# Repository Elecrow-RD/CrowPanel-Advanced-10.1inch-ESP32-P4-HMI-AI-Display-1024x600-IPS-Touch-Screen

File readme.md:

### 1, Product picture

### 2, Product version number

|      | Hardware | Software | Remark |
| ---- | -------- | -------- | ------ |
| 1    | V1.0     | V1.0     | old |
| 1    | V1.1     | V1.1     | old |
| 1    | V1.2     | V1.2     | latest |

**Version 1.1 Update**

The C6 module version 1.1 adds support for 4-wire SDIO communication. Additionally, the arrangement of the SDIO pins has been adjusted, with the pin mappings of the data lines D0–D3 changing from **IO14, IO15, IO16, IO17** to **IO17, IO16, IO15, IO14**. 

**Version 1.2 Update** 

Based on the V1.1 version, V1.2 further optimized the communication stability of the LoRa wireless module. At the same time, the signal pins of the wireless module socket were re-allocated: the original **IO53 and IO54** were adjusted to **IO27 and IO28** respectively, and correspondingly, **IO27 and IO28** were adjusted to **IO53 and IO54** respectively.

### 3, product information

| **Main Chip-ESP32-P4NRW32**                  |                                                              |
| -------------------------------------------- | ------------------------------------------------------------ |
| CPU/SoC                                      | **ESP32-P4**RISC-V 32-bit dual-core processor for HP systems, running at up to 400 MHz; RISC-V 32-bit single-core processor for LP systems, running at up to 40 MHz |
| System Memory                                | 768 KB L2MEM（HP）32 KB SRAM（LP）8 KB TCM 32 MB PSRAM       |
| Memory                                       | 128 KB ROM（HP）16 KB ROM（LP）16 MB Flash                   |
| Development Environment                      | ESP-IDF、Arduino IDE                                         |
| **Screen**                                   |                                                              |
| Size                                         | 10.1 inch                                                    |
| Resolution                                   | 1024*600                                                     |
| Display Panel                                | IPS Panel                                                    |
| Touch Panel                                  | Capacitive Touch, Single/5-point Touch                       |
| Viewing Angle                                | 178°                                                         |
| Brightness                                   | 400 cd/m²(Typ.)                                              |
| Color Depth                                  | 16.7M (8-bit)                                                |
| **Wireless Communication - Onboard Antenna** |                                                              |
| WiFi                                         | Support 2.4GHz(Wi-Fi6), 802.11a/b/g/n                        |
| Bluetooth                                    | Support Bluetooth 5.3 and BLE                                |
| Other                                        | Zigbee、LoRa、nRF2401、Matter、Thread and Wi-Fi Halow (Optional) |
| **Interface/Function**                       |                                                              |
| Interface                                    | USB2.0, UART, I2C, GPIO female headers, SD card holder, battery socket, speaker jack, camera header, module female headers, etc. |
| Function                                     | Audio amplifier, battery charge management, USB to UART, dual microphones, etc. |
| **Button/LED Indicator**                     |                                                              |
| Reset Button                                 | Yes, press to reset device                                   |
| Boot Button                                  | Yes, press and hold the power button to burn the program     |
| Power Button                                 | Switch On/Off                                                |
| PWR                                          | Device power on/off indication                               |
| CHG                                          | Lithium battery charging status, Low battery state           |
| **Other**                                    |                                                              |
| Installation method                          | All around mounting holes(M3 3.2mm), embedded, shell assembly |
| Operating temperature                        | -20~70 °C                                                    |
| Storage temperature                          | -30~80 °C                                                    |
| Power Input                                  | 5V/2A, USB or UART terminal                                  |
| Dimensions                                   | 248*147mm                                                    |

### Functional description of the product's internal interfaces:

| Pin Name | Description                                                  | Connector Type |
| :------- | :----------------------------------------------------------- | :------------- |
| SPK      | Output audio signals to connect to speakers. The main board comes with a power amplifier chip circuit. | PH2.0-2P       |
| PWR      | Power LED.                                                   |                |
| RST      | Reset button. Press it to reset the system.                  |                |
| boot     |                                                              |                |
| UART1    | Builds communication between Logic modules, including the serial communication module and the print module. | HY2.0-4P       |
| I2C      | Builds communication between Logic modules, including the serial communication module and the print module. | HY2.0-4P       |
| UART3-IN | Input power supply and serial communication functionality    | XH2.54-4P      |
| BAT      | Connect the lithium battery. (with battery charging circuit) | PH2.0-2P       |

### 4, Use the driver module

| Name | dependency library                                |
| ---- | ------------------------------------------------- |
| LVGL | lvgl/lvgl@9.1(V1.2)<br />lvgl/lvgl@8.3(V1.0/V1.1) |

### 5,Quick Start
##### ESP-IDF starts

**Note**: This is an IDF course. Before proceeding, ensure you have **Visual Studio Code** and the **IDF **environment installed. The IDF version must be **5.4.2** or higher.

1.Right-click on an empty space in the project folder and select "Open with VS Code" to open the project.

2.In the IDF plug-in, select the port, then compile and flash

### 6,Folder structure.
|--3D file： Contains 3D model files (.stp) for the hardware. These files can be used for visualization, enclosure design, or integration into CAD software.

|--Datasheet: Includes datasheets for components used in the project, providing detailed specifications, electrical characteristics, and pin configurations.

|--Eagle_SCH&PCB: Contains **Eagle CAD** schematic (`.sch`) and PCB layout (`.brd`) files. These are used for circuit design and PCB manufacturing.

|--example: Provides example code and projects to demonstrate how to use the hardware and libraries. These examples help users get started quickly.

|--factory_firmware: Stores pre-compiled factory firmware that can be directly flashed onto the device. This ensures the device runs the default functionality.

|--factory_sourcecode:  Contains the source code for the factory firmware, allowing users to modify and rebuild the firmware as needed.

|--libraries: Includes necessary libraries required for compiling and running the project. These libraries provide drivers and additional functionalities for the hardware.

### 7,Pin definition

#### ESP32-P4 10.1 inch and IPS Display Wiring Pins:
**DSI = Display Serial Interface**is a high-speed, low-power display interface standard defined by the MIPI Alliance, most commonly used in smartphones, tablets, Raspberry Pi devices, and embedded Linux systems.

DSI Pin connection

DSI_DATAN0--IO40

DSI_DATAN0--IO39

DSI_DATAN0--IO36

DSI_DATAN0--IO35

DSI_CLKN--IO37

DSI_CLKP--IO38

DSI_REXT--IO34

#### ESP32-P4 and Touch Driver Wiring：
i2c address: 0x5D/0x14.(The INT pin level during reset of the GT911 touch chip determines the device address.)

INT Low Level(0x5D);

INT High Level(0x14).

Pin connection

I2C1_SCL(IO46)

I2C1_SDA(IO45)

INT_TP(IO42)

RESET_TP(IO40)

#### ESP32-P4 and wireless module wiring pins：

Output voltage: 3.3V Output current: 1A max. Use: The power supply communicates with the wireless module.

Pin connection

#define RADIO_GPIO_CLK 8

#define RADIO_GPIO_MISO 7

#define RADIO_GPIO_MOSI 6

#ifdef CONFIG_BSP_SX1262_ENABLED

#define SX1262_GPIO_BUSY 9

#define SX1262_GPIO_IRQ 53

#define SX1262_GPIO_NRST 54

#define SX1262_GPIO_NSS 10

#ifdef CONFIG_BSP_NRF2401_ENABLED

#define NRF24_GPIO_IRQ 9

#define NRF24_GPIO_CE 53

#define NRF24_GPIO_CS 54

ESP32-P4 and Audio out：

Pin connection

#define AUDIO_GPIO_LRCLK    21   // GPIO pin number for LRCLK (Left-Right Clock)

#define AUDIO_GPIO_BCLK     22   // GPIO pin number for BCLK (Bit Clock)

#define AUDIO_GPIO_SDATA    23   // GPIO pin number for SDATA (Serial Data)

#define AUDIO_GPIO_CTRL     30   // GPIO pin number for audio amplifier control

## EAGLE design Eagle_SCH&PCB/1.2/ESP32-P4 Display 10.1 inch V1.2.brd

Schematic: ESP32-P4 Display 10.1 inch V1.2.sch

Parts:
C1, C2, C3, C10, C17, C86, C143, C160: 1uF; 0603
C4: 10uF/NC; 0603
C5, C7, C9, C36, C40, C41, C43, C45, C46, C50, C60, C61, C63, C72, C73, C108, C113, C115, C130, C132, C145: 100nF; C0402
C6, C8, C42, C44, C47, C48, C49, C56, C71, C107, C112, C114, C116: 10uF; C0402
C11, C15, C19, C20, C21, C35, C37, C52, C53, C54, C75, C76, C77, C80, C81, C82, C84, C135, C147, C150, C151, C152, C154, C156, C157, C158, C162, C170: 100nF; 0603
C12, C27, C28, C32: 10uF/10V+; 0603
C13, C18: 22uF; C0805
C14, C16, C38, C74, C78, C79, C83, C149, C153, C155, C159: 10uF; 0603
C22, C102: 1uF_NC; 0603
C23, C24, C103, C104: 47uF_NC; 0603
C25, C69, C89, C101, C163, C164, C165, C166, C167, C168, C169: 22pF; C0402
C26, C31: 22pF; 0603
C29, C30: 12pF; C0402
C33, C34: 15pF; C0402
C39: 100nF_NC; C0402
C51, C55, C57, C58, C59, C64, C65, C66, C117, C118, C119, C120, C121, C122, C123, C124, C125, C126, C127, C128, C129, C131, C133, C137, C138, C139, C140, C141, C142, C146: 1uF; C0402
C62: 10nF; C0402
C67, C68, C85, C105, C106, C161: 1nF; 0603
C70: 10UF; 0603
C87: 15pF; 0603
C88: 10UF_NC; 0603
C90, C99, C110: 10uF/25V; 0603
C91, C100, C111: 100nF/50V; 0603
C92: 22uF/16V; C0805
C93: 10nF/25V; 0603
C94: 10uF/25V; C0402
C95: 100nF/50V; C0402
C96, C97: 1uF/25V; 0603
C98, C109: 1uF/50V; 0603
C134, C148: 47uF; 0603
C136, C144: 22uF; 0805
C171, C172, C173, C174, C175, C176, C177: NC; C0402
D1: KT-0603RYG; LED_KT-0603RYG
D2, D007, D10: DSS34; D_SOD123FL
D003: NC/DSS34; D_SOD123FL
D4, D008, D11: 1N5817WS; D_SOD323
D005, D012, D013, D015, D017, D018: LMBR140ET1G
D14: Red; LED0603
D016: MM1W18_18V; LMSZ5233BT1G
D020: LMSZ5233BT1G_-6V; LMSZ5233BT1G
FB2, FB3, FB10, FB11: 1K/磁珠_NC; L0603
FB4, FB5, FB6, FB13: 0R/800mA; L0402
FB7, FB8, FB9, FB12: 1K/磁珠; L0603
FB14: 0R/800mA; R0402
FB15, FB17, FB18, FB19, FB20: 0R/2A; L0603
FB16: 0R/800mA_NC; L0603
FB21: 0R/2A; L0805
FPC1: AFC24-S24FIA-00; FPC-SMD_P0.50-24P_QCHF-SM-H2.0
FPC2: FPC-6PIN-0.5MM
IC1: ESP32-C6-MINI-1-N4; ESP32C6MINI1N4
IC2: ME6211C18M5G-N; SOT95P282X145-5N
IC3: ME6211C28M5G-N; SOT95P282X145-5N
IC4: ME6211C18M5G-N_NC; SOT95P282X145-5N
IC5: ES7210; QFN40P400X400X80-33N
IC6: ES8311; QFN40P300X300X60-21N
IC7, IC8: ME6211C33M5G-N; SOT95P282X145-5N
IC11: W25Q128JVSIQ; SOIC127P790X216-8N
J1, J16: TYPEC-3.0-16P-SMD; USB-3.0TYPEC-SMD
J2, J13: HY2.0-4P-SMT; CONNECTOR_4P-SMD-2.0
J3, J4, J6: PH2.0WT-2PIN
J5: HOLDER-MICROSD-9P; 9P-SMD-W/-RING
J7: CONN_12X22X12-SMD1; 2X12-SMD1
J8: HC-PZ200-8.7L-1X4PZ1; TEST-PIN-4-2.0MM
J9, J11: HEADER-7P-18.28X2.5; H7-2.54-18.28X2.5X5MM
J10: XH2.54-4P-SMT; XH2.54-4P-SMD
J12, J14, J15, J17: THO-M3.25MM-HOLE; THO-M3.2*5MM-HOLE
J21: C23398852_30P_0.5MM_下接_FC-05A30P11H20
K3, K4: KEY-4.5X4.5; KEY-4.5X4.5-SMD
L1, L6: 2.2μH_C5179446; 1008(2520)
L2, L5: 4.7uH_C45385206_2.4A; 1008(2520)
L3: 0R; L0603
L4: NC; L0603
P1, P2, P3, P5, P6, P7, P8, P9, P10, P11, P13, P14, P15, P18, P19, P20, P21, P25, P26, P28, P31, P32, P33, P34, P35, P36, P39, P40, P41, P43, P44, P46, P47, P51, P54, P55, P56, P63, P64, P66, P67, P68, P69, P70, P72, P73, P77: TEST_PADPAD-1.5MM; TEST_PAD-1.5MM
Q1, Q2, Q4, Q6, Q7, Q8, Q9: BSS138W_SOT323; MOS_SOT323
Q3, Q5: XR65P02D; PDFN3333
Q10, Q11: AO3401_NC; PMOS_SOT23
R1, R5, R9, R18, R53, R54, R61, R66, R67, R71, R77, R87, R91, R106, R116, R160, R180, R181: 10K; R0603@1
R2, R165: 100K; R0603@1
R3, R4, R17, R26, R47, R50, R96, R101: 5.1K; R0603@1
R6, R7, R8, R10, R13, R24, R55, R60, R65, R76, R103, R118, R119, R164, R184, R186: 0R; R0603@1
R11: 22.1K; R0603
R12, R19, R20, R36, R37, R38, R39, R41, R42, R43, R44, R70, R80, R88, R89, R90, R92, R95, R99, R100, R102, R104, R105, R109, R110, R111, R124, R125, R126, R128, R130, R146, R148, R170, R177, R190, R191, R192, R193: 0R; R0402
R14, R21: NC/499K; R0603
R15, R27, R28, R29, R30, R33, R72, R73, R140, R333: 10K; R0402
R16, R31, R32, R69: 2K; R0603-SP
R22, R45, R46, R51, R52, R56, R57, R58, R59, R62, R78: 4.7K; R0603@1
R23: 0R; C0402
R25: 0R; R0603-SP
R34, R133, R135, R136, R137, R138: 22R; R0402
R35: NC/10M; R0402
R40, R107, R127, R161, R162: 0R_NC; R0402
R48, R49, R151, R194, R216, R217, R332: 0R; 0402
R63, R64, R68, R108, R122, R123: 100K; R0402
R74, R93, R94, R97, R98: 2K; R0603@1
R75: 2K_NC; R0603@1
R79, R147, R185: OR; R0603-SP
R81, R82, R83, R84, R85, R86: 51K; R0402
R112, R113, R114, R115, R129, R149: 0R_NC; R0603@1
R117, R139: 100K_NC; R0603@1
R120, R121: 5.1K_NC; R0603@1
R131, R171: 10K/NC; R0402
R132, R134: OR/NC; R0402
R141, R142, R144, R145: OR; R0402
R143: 50K_NC; R0603-SP
R152, R153, R154, R155, R156, R157: 100R; R0402
R158: 4.02K; R0402
R159: 0.75R; R0603-SP
R163: NC; R0603-SP
R166: 210K; R0603
R167: 12K; R0603
R168: 1.5K; R0402
R169: 1K; R0402
R172, R174: 220R; R0603
R173, R175: 51K; R0603@1
R178, R179: 20K; R0603
R182: 0R; R0805
R187, R189: 39k; R0603@1
R188: 100k; R0603@1
R210: NC/10K; R0603@1
SW1: switch_6pin; SWITCH_6PIN_2P
U1: CH340K; ESOP-10-EP-150MIL
U2: TP4059-SOT23-6; SOT23-6L
U3, U13: NS4168-NC; NS4168-ESOP-8
U4: NS4263B; SOP16
U5: STC8H1K08-36I; TSSOP20
U6: MT9201; COOPER_SOT23-6
U7: ESP32-P4NRW32; IC_ESP32-P4NRW32
U8: UMH3NTN; SOP65P210X100-6N
U9: RY3420/C370754; SOT95P280X145-5N
U10: MT3406_C22462728; SOT95P280X145-5N
U16: MT3608; SOT95P280X145-6N
U176: BRAIN1_LMA3526B3811; BRAIN1_MIC-SMD_5P-L3.5-W2.7
Y2: 40MHZ; X322540MPB4SI
Y3: 24Mhz; 24MHZ_1631-24003-BTKEYA
Y4: 32.768K; NORDIC_NRF_XTAL_3215_N

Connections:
3V3$: C2.2, U1.10 (V3)
+5V_IN: D2.+, D4.+, J10.3, P14.P$1, R46.1, R51.1
+VBUS1: D10.+, D11.+, J1.A4, J1.A9, J1.B4, J1.B9, P1.P$1
+VBUS2: D007.+, D008.+, J16.A4, J16.A9, J16.B4, J16.B9, P77.P$1
ADC_AVDD_3V3: C132.1, C133.2, FB5.2, IC5.22 (VDDA), IC5.23 (VDDM)
ADC_DVDD_3V3: C130.1, C131.2, FB4.2, IC5.6 (VDDP), IC5.7 (VDDD), R73.1
ADC_VBAT: C161.2, R187.2, R188.1, U5.13 (P3.2/ADC10)
AGND: C102.2, C103.2, C104.2, C105.1, C106.1, C134.1, C143.1, C148.1, C154.2, FB19.2, FB21.2, J4.P$3, J4.P$4, R79.2, R143.1, R185.1, U4.2, U4.7, U4.15, U13.7 (GND), U13.9 (PE)
AGND1: C72.1, C117.1, C118.1, C119.1, C120.1, C121.1, C122.1, C127.2, C128.2, C129.2, C132.2, C133.1, C137.1, C138.2, C139.2, C142.2, C145.2, C146.1, IC5.21 (GNDA), IC6.10 (AGND), R144.1, R145.2, R171.2, R182.2, U176.P$1 (5)
AGND3: C22.2, C23.2, C24.2, C67.1, C68.1, FB20.2, U3.7 (GND), U3.9 (PE)
AUDIO_CTRL: Q10.3 (D), R117.2, R139.2
AUDIO_OUT_3V3: C134.2, C148.2, C154.1, FB15.2, U4.4, U4.13
AUDIO_OUT_SD: Q10.1 (G), R71.1, R147.1, U7.60 (GPIO30)
AUDIO_VDD1: C102.1, C103.1, C104.1, FB17.1, U13.6 (VDD)
AUDIO_VDD2: C22.1, C23.1, C24.1, FB18.1, U3.6 (VDD)
AUDIO_VDD_3V3: C152.2, C153.2, FB4.1, FB5.1, FB6.1, FB14.1, FB16.2, IC7.5 (VOUT)
AVDD_2V8: C82.2, C83.2, FPC1.1, FPC1.2, IC3.5 (VOUT)
C6_EN: C15.1, IC1.8 (EN), P39.P$1, R77.1, U7.63 (GPIO32)
C6_IO8: IC1.22 (IO8), R87.2
C6_IO9_BOOT: IC1.23 (IO9), P36.P$1
C6_RXD0: IC1.30 (RXD0), P21.P$1
C6_TXD0: IC1.31 (TXD0), P25.P$1
C6_VDD_3V3: C11.1, C14.2, IC1.3 (3V3), R76.1, R77.2, R81.1, R82.1, R83.1, R84.1, R85.1, R86.1, R87.1
CODEC_3V3: C145.1, C146.2, FB13.2, FB14.2, IC6.3 (PVDD), IC6.4 (DVDD)
CSID0_P: R153.1, U7.43 (CSI_DATAP0)
CSI_CLK_N: FPC1.19, R156.2
CSI_CLK_P: FPC1.18, R157.2
CSI_D0_N: FPC1.16, R152.2
CSI_D0_P: FPC1.15, R153.2
CSI_D1_N: FPC1.22, R154.2
CSI_D1_P: FPC1.21, R155.2
CSI_RESET: FPC1.8, Q4.2 (S), R57.2
CSI_SCL: FPC1.4, Q7.2 (S), R62.2
CSI_SDA: FPC1.5, Q6.2 (S), R56.2
DA1: J5.8 (DATA1), P47.P$1, R15.1
DA2: J5.1 (DATA2), P72.P$1, R30.1
DOVDD_1V8: C77.2, C78.2, C84.2, C85.2, FPC1.9, IC2.5 (VOUT), Q4.1 (G), Q6.1 (G), Q7.1 (G), R56.1, R57.1, R62.1, R67.2, Y3.4 (4_VDD)
DOWNLOAD_BOOT: R60.1, R106.2
DSI_CLK_N: J21.18, R100.1
DSI_CLK_P: J21.17, R102.1
DSI_DATA0_N: J21.24, R190.1
DSI_DATA0_P: J21.23, R92.1
DSI_DATA1_N: J21.21, R95.1
DSI_DATA1_P: J21.20, R99.1
DTR: R5.2, U1.4 (DTR#), U8.4 (E2)
EN_DCDC: R13.2, U7.79 (EN_DCDC)
ESP32_LDO1: C58.1, R105.2, U7.71 (VFB1/VO1)
ESP32_LDO2: C57.1, R40.2, U7.72 (VFB2/VO2)
ESP32_LDO3: C59.1, R80.2, U7.73 (VFB3/VO3)
ESP32_LDO4: C66.1, R109.2, U7.74 (VFB4/VO4)
FB_DCDC: C31.1, R14.2, R21.1, R103.1, U10.5 (FB)
FLASH_CK: IC11.6 (CLK), U7.32 (FLASH_CK)
FLASH_CS: IC11.1 (/CS), R333.1, U7.27 (FLASH_CS)
FLASH_D: IC11.5 (DI_(IO0)), U7.33 (FLASH_D)
FLASH_HOLD: IC11.7 (/HOLD_OR_/RESET_(IO3)), U7.31 (FLASH_HOLD)
FLASH_Q: IC11.2 (DO_(IO1)), U7.28 (FLASH_Q)
FLASH_WP: IC11.3 (/WP_(IO2)), U7.29 (FLASH_WP)
GND: C1.1, C2.1, C3.1, C4.1, C5.2, C6.1, C7.2, C8.1, C9.2, C10.1, C11.2, C12.2, C13.2, C14.1, C15.2, C16.1, C17.1, C18.2, C19.2, C20.1, C21.1, C25.2, C27.1, C28.2, C29.2, C30.2, C32.1, C33.2, C34.1, C35.1, C36.2, C37.1, C38.1, C39.2, C40.2, C41.2, C42.1, C43.2, C44.1, C45.2, C46.2, C47.1, C48.1, C49.1, C50.2, C51.2, C52.1, C53.1, C54.1, C55.2, C56.1, C57.2, C58.2, C59.2, C60.2, C61.2, C62.2, C63.2, C64.2, C65.2, C66.2, C69.2, C70.2, C71.1, C73.2, C74.1, C75.1, C76.1, C77.1, C78.1, C79.1, C80.1, C81.1, C82.1, C83.1, C84.1, C85.1, C86.1, C87.1, C88.2, C90.2, C91.2, C92.2, C94.2, C95.2, C98.2, C99.2, C100.2, C107.1, C108.2, C109.2, C110.2, C111.2, C112.1, C113.2, C114.1, C115.2, C116.1, C130.2, C131.1, C136.1, C144.1, C149.1, C150.1, C151.1, C152.1, C153.1, C155.1, C156.1, C157.1, C158.1, C159.1, C160.1, C161.1, C162.1, C163.2, C164.2, C165.2, C166.2, C167.2, C168.2, C169.2, C170.2, C171.1, C172.1, C173.1, C174.1, C175.1, C176.1, C177.1, D14.-, D016.2, D018.1, D020.1, FB19.1, FB20.1, FB21.1, FPC1.3, FPC1.6, FPC1.10, FPC1.12, FPC1.17, FPC1.20, FPC1.25, FPC1.26, FPC2.4, FPC2.7, FPC2.8, IC1.1 (GND_1), IC1.2 (GND_2), IC1.11 (GND_3), IC1.14 (GND_4), IC1.36 (GND_5), IC1.37 (GND_6), IC1.38 (GND_7), IC1.39 (GND_8), IC1.40 (GND_9), IC1.41 (GND_10), IC1.42 (GND_11), IC1.43 (GND_12), IC1.44 (GND_13), IC1.45 (GND_14), IC1.46 (GND_15), IC1.47 (GND_16), IC1.48 (GND_17), IC1.49 (GND_18), IC1.50 (GND_19), IC1.51 (GND_20), IC1.52 (GND_21), IC1.53 (GND_22), IC1.54 (GND_23), IC1.55 (GND_24), IC1.56 (GND_25), IC1.57 (GND_26), IC1.58 (GND_27), IC1.59 (GND_28), IC1.60 (GND_29), IC1.61 (GND_30), IC2.2 (VSS), IC3.2 (VSS), IC4.2 (VSS), IC5.8 (GNDD), IC5.33 (EP), IC6.5 (DGND), IC6.20 (CE), IC6.21 (EP), IC7.2 (VSS), IC8.2 (VSS), IC11.4 (GND), J1.A1, J1.A12, J1.B1, J1.B12, J1.P$1, J1.P$2, J1.P$3, J1.P$4, J2.4, J2.SS1, J2.SS2, J3.P$2, J3.P$3, J3.P$4, J5.6 (VSS), J5.G1, J5.G2, J5.G3, J5.G4, J6.P$3, J6.P$4, J7.7, J7.8, J7.10, J7.21, J7.22, J7.23, J7.24, J8.4, J9.6, J9.6-6 (6), J10.4, J10.5 (SS1), J10.6 (SS2), J12.P$1, J13.4, J13.SS1, J13.SS2, J14.P$1, J15.P$1, J16.A1, J16.A12, J16.B1, J16.B12, J16.P$1, J16.P$2, J16.P$3, J16.P$4, J17.P$1, J21.10, J21.13, J21.16, J21.19, J21.22, J21.25, J21.31, J21.32, K3.1, K4.1, P10.P$1, P15.P$1, P28.P$1, P31.P$1, P43.P$1, P66.P$1, P67.P$1, P68.P$1, P69.P$1, P70.P$1, R3.1, R4.2, R11.2, R16.1, R18.1, R21.2, R33.2, R64.1, R72.1, R96.1, R101.2, R104.1, R108.1, R123.1, R158.2, R159.1, R160.2, R163.1, R167.1, R169.1, R173.1, R175.1, R182.1, R188.2, SW1.1 (1_2B), SW1.6 (6_1B), U1.3 (GND), U1.EP, U2.2 (GND), U5.10 (GND), U6.2 (2-GND), U7.105 (GND), U9.2 (GND), U10.2 (GND), U16.2 (2_GND), Y2.2 (GND_1), Y2.4 (GND_2), Y3.2 (2_GND)
I2C1_SCL: FPC2.1, Q9.2 (S), R97.2, U7.88 (GPIO46)
I2C1_SCL_3V3: IC6.1 (CCLK), J11.2, J11.2-2 (2), J13.1, Q9.3 (D), R93.2, R119.1, R125.1
I2C1_SDA: FPC2.2, Q8.2 (S), R98.2, U7.87 (GPIO45)
I2C1_SDA_3V3: IC6.19 (CDATA), J11.3, J11.3-3 (3), J13.2, Q8.3 (D), R94.2, R118.1, R124.1
I2C2_SCL: Q7.3 (D), R59.2, R89.2
I2C2_SDA: Q6.3 (D), R22.2, R90.2
I2SOUT_LRCK1: R149.2, U13.2 (LRCLK)
I2SOUT_LRCK2: P35.P$1, R114.2, U3.2 (LRCLK)
I2SOUT_SCLK1: R129.2, U13.3 (BCLK)
I2SOUT_SCLK2: P34.P$1, R113.2, U3.3 (BCLK)
I2SOUT_SD1: R112.2, U13.4 (SDATA)
I2SOUT_SD2: P33.P$1, R115.2, U3.4 (SDATA)
I2S_LRCK: R114.1, R130.1, R149.1, U7.23 (GPIO21)
I2S_LRCK_N: IC5.10 (LRCK), IC6.8 (LRCK), R130.2
I2S_MCLK: R126.1, R127.1, U7.52 (GPIO24)
I2S_MCLK_N: IC5.5 (MCLK), IC6.2 (MCLK), R126.2
I2S_SCLK: R113.1, R128.1, R129.1, U7.24 (GPIO22)
I2S_SCLK_N: IC5.9 (SCLK), IC6.6 (SCLK/DMIC_SCL), R128.2
I2S_SDIN1_N: IC5.11 (SDOUT1/TDMOUT)
I2S_SDIN2: R161.1, R162.1, U7.55 (GPIO26)
I2S_SDIN2_N: IC5.12 (SDOUT2/TDMIN), R161.2
I2S_SDOUT: R111.1, R112.1, R115.1, U7.25 (GPIO23)
I2S_SDOUT_N: IC6.9 (DSDIN), R111.2
INLN: C147.1, R148.2
INLN1: R179.1, U4.6
INRN: C135.1, R146.2
INRN1: R178.1, U4.11
INT_TP: FPC2.3, R75.2, U7.83 (GPIO42)
IO1: R89.1, U7.14 (GPIO13)
IO8: R217.1, U7.8 (GPIO8)
IO9_W: R151.2, U7.10 (GPIO9)
IO10_W_BUSY: R194.2, U7.11 (GPIO10)
IO46_CSI_RESET: Q4.3 (D), R58.2, R88.2
LCD_AVDD_9V6: C92.1, C93.1, D005.2, D013.1, J21.9, P19.P$1, R166.2, R168.2
LCD_BK_EN: R160.1, U6.4 (4-EN), U7.61 (GPIO31)
LCD_BK_POWER: Q11.1 (G), R180.1, U7.58 (GPIO29)
LCD_BK_VDD: C13.1, C17.2, L5.1, Q11.3 (D), R184.2, U6.6 (6-VIN)
LCD_RESET: J21.27, R69.2, U7.82 (GPIO41)
LCD_VCOM_3V3: C94.1, C95.1, J21.30, P20.P$1, R168.1, R169.2
LCD_VDD: C37.2, C38.2, C52.2, C53.2, IC4.5 (VOUT), J21.28, J21.29, P46.P$1, R63.2, R65.1, R68.2, R122.2
LCD_VGH_18V: C99.1, C100.1, D016.1, J21.3, P18.P$1, R172.1, R173.2
LCD_VGL_-6V: C110.1, C111.1, D020.2, J21.4, P44.P$1, R174.1, R175.2
LED+: C18.1, C19.1, D003.-, D012.1, P63.P$1, R25.1, U6.5 (5-OV)
LED-: J21.7, J21.8, P64.P$1, R159.2, R163.2, U6.3 (3-FB)
MIC1N: C89.2
MIC1P: C101.2
MIC2N: C125.2, R141.2
MIC2P: C126.2, R142.2
MIC2_1: R132.2, R142.1, U176.1
MIC2_2: R131.1, R141.1, R145.1, R171.1, U176.2
MIC2_3: R134.1, R144.2, U176.3
MIC2_VDD_3V3: C72.2, FB6.2, U176.4
MIC3N: C124.1, R170.2
MIC3P: C123.1, R177.2
MIC_L/R: R131.2, U7.22 (GPIO20)
MIC_MCLK: R127.2, R134.2
MIC_SD2: R132.1, R162.2
unnamed: R1.1, U9.1 (EN)
unnamed: L1.1, U9.3 (SW)
unnamed: FB7.1, U4.12
unnamed: FB10.1, U13.8 (VOP)
unnamed: R6.1, U1.1 (UD+)
unnamed: R7.1, U1.2 (UD-)
unnamed: R5.1, U8.2 (B1)
unnamed: R9.1, U8.5 (B2)
unnamed: J1.B5, R3.2
unnamed: R8.2, U1.9 (RXD)
unnamed: R10.2, U1.8 (TXD)
unnamed: R16.2, U2.6 (PRO)
unnamed: C26.1, R2.2, R11.1, U9.5 (FB)
unnamed: L6.1, U10.3 (SW)
unnamed: C151.2, IC7.3 (CE), R181.1
unnamed: R13.1, R210.2, U10.1 (EN)
unnamed: C143.2, U4.10
unnamed: R185.2, U4.8
unnamed: D1.3, R31.1, R121.1
unnamed: D1.4, R32.1, R120.1
unnamed: D14.+, R26.1
unnamed: J21.1, J21.2, P56.P$1, R25.2
unnamed: C174.2, J9.1, J9.1-1 (1), R49.1
unnamed: C177.2, J11.1, J11.1-1 (1), R48.1
unnamed: FB8.1, U4.14
unnamed: Q5.4 (4_G), R78.1, SW1.2 (2_COM2), SW1.5 (5_COM1)
unnamed: J1.A5, R4.1
unnamed: R79.1, U4.16
unnamed: C28.1, R24.1, R210.1, U10.4 (VIN)
unnamed: R90.1, U7.13 (GPIO12)
unnamed: R88.1, U7.12 (GPIO11)
unnamed: R190.2, U7.40 (DSI_DATAN0)
unnamed: R92.2, U7.39 (DSI_DATAP0)
unnamed: C30.1, R35.1, U7.1 (GPIO1), Y4.2
unnamed: C29.1, R35.2, U7.104 (GPIO0), Y4.1
unnamed: R95.2, U7.36 (DSI_DATAN1)
unnamed: R99.2, U7.35 (DSI_DATAP1)
unnamed: R100.2, U7.37 (DSI_CLKN)
unnamed: C147.2, R179.2
unnamed: R102.2, U7.38 (DSI_CLKP)
unnamed: R103.2, U7.78 (FB_DCDC)
unnamed: R104.2, U7.34 (DSI_REXT)
unnamed: C21.2, IC4.3 (CE), R53.1
unnamed: C135.2, R178.2
unnamed: FB2.1, U3.8 (VOP)
unnamed: FB11.1, U13.5 (VON)
unnamed: FB3.1, U3.5 (VON)
unnamed: R117.1, U3.1 (CTRL)
unnamed: R118.2, U5.3 (MISO/P1.4)
unnamed: R119.2, U5.4 (SCLK/P1.5)
unnamed: R139.1, R143.2, U13.1 (CTRL)
unnamed: IC5.3 (CDATA), R124.2
unnamed: IC5.4 (CCLK), R125.2
unnamed: FB9.1, U4.3
unnamed: C157.2, IC8.3 (CE), R116.1
unnamed: R164.2, U5.12 (P3.1/ADC9)
unnamed: R186.2, U5.11 (P3.0/ADC8)
unnamed: FB12.1, U4.5
unnamed: C124.2, IC5.32 (MIC3N)
unnamed: C89.1, IC5.15 (MIC1N)
unnamed: C101.1, IC5.16 (MIC1P)
unnamed: C162.2, R189.2, U5.7 (NRST/PWM6/P5.4)
unnamed: R332.1, U7.7 (GPIO7)
unnamed: R216.1, U7.6 (GPIO6)
unnamed: R191.2, U7.80 (GPIO39)
unnamed: R192.2, U7.84 (GPIO43)
unnamed: R193.2, U7.86 (GPIO44)
unnamed: R158.1, U7.48 (CSI_REXT)
unnamed: R157.1, U7.44 (CSI_CLKP)
unnamed: R156.1, U7.45 (CSI_CLKN)
unnamed: R155.1, U7.47 (CSI_DATAP1)
unnamed: R154.1, U7.46 (CSI_DATAN1)
unnamed: R152.1, U7.42 (CSI_DATAN0)
unnamed: J16.B5, R96.2
unnamed: J16.A5, R101.1
unnamed: C176.2, J11.5, J11.5-5 (5), R151.1
unnamed: C175.2, J11.6, J11.6-6 (6), R194.1
unnamed: C123.2, IC5.31 (MIC3P)
unnamed: C122.2, IC5.30 (REFQ34)
unnamed: C121.2, IC5.29 (REFP34)
unnamed: C76.2, IC2.3 (CE), R61.1
unnamed: C81.2, IC3.3 (CE), R66.1
unnamed: C86.2, R67.1, Y3.1 (1_EN)
unnamed: C120.2, IC5.28 (MIC4P)
unnamed: C119.2, IC5.27 (MIC4N)
unnamed: C118.2, IC5.26 (MICBIAS34)
unnamed: C117.2, IC5.25 (REFQM)
unnamed: C129.1, IC5.24 (MICBIAS12)
unnamed: C125.1, IC5.20 (MIC2N)
unnamed: C126.1, IC5.19 (MIC2P)
unnamed: C127.1, IC5.18 (REFQ12)
unnamed: C128.1, IC5.17 (REFP12)
unnamed: R147.2, U4.1
unnamed: C97.2, D017.1, D018.2
unnamed: IC5.1 (AD0), R73.2
unnamed: IC5.2 (AD1), R72.2
unnamed: C139.1, IC6.14 (DACVREF)
unnamed: C137.2, IC6.16 (VMID)
unnamed: C138.1, IC6.15 (ADCVREF)
unnamed: C140.1, IC6.13 (OUTN)
unnamed: C141.1, IC6.12 (OUTP)
unnamed: C142.1, FB13.1, IC6.11 (AVDD)
unnamed: D003.+, D012.2, L5.2, U6.1 (1-SW)
unnamed: C96.1, C97.1, D013.2, L2.2, U16.1 (1_SW)
unnamed: R165.2, U16.4 (4_EN)
unnamed: C96.2, D005.1, D015.2
unnamed: C93.2, R166.1, R167.2, U16.3 (3_FB)
unnamed: C98.1, D015.1, R172.2
unnamed: C140.2, R146.1, R170.1
unnamed: C109.1, D017.2, R174.2
unnamed: C141.2, R148.1, R177.1
P4_IO2: J7.9, U7.2 (GPIO2)
P4_IO3: J7.11, U7.3 (GPIO3)
P4_IO4: J7.13, U7.4 (GPIO4)
P4_IO5: J7.15, U7.5 (GPIO5)
P4_IO25: J7.17, U7.53 (GPIO25)
P4_IO35: R55.2, U7.66 (GPIO35)
P4_IO36: R60.2, U7.68 (GPIO36)
P4_IO49: J7.19, U7.92 (GPIO49)
P4_IO50: J7.20, U7.93 (GPIO50)
P4_IO51: J7.18, U7.94 (GPIO51)
P4_IO52: J7.16, U7.95 (GPIO52)
P4_IO53: J7.14, U7.97 (GPIO53)
P4_IO54: J7.12, U7.98 (GPIO54)
P4_RST_EN: C35.2, K4.2, R54.2, U7.103 (CHIP_PU), U8.6 (C1)
P4_RXD2: R48.2, U7.57 (GPIO28)
P4_TXD2: R49.2, U7.56 (GPIO27)
P4_VBAT: C9.1, C42.2, R20.1, U7.102 (VBAT)
POWER_CHRG: R50.1, R120.2, U2.1 (CHG), U5.14 (P3.3/ADC11)
POWER_DONE: R47.1, R121.2, U2.5 (STD), U5.15 (P3.4/ADC11)
POWER_G_LED: R31.2, U5.17 (P3.6/ADC14)
POWER_R_LED: R32.2, U5.16 (P3.5/ADC13)
RESET_TP: FPC2.6, R74.2, U7.81 (GPIO40)
RTS: R9.2, U1.6 (RTS#), U8.1 (E1)
RXD0: R10.1, U7.70 (GPIO38)
RXD1: J2.1, U7.90 (GPIO48)
RXD3: Q2.2 (S), R45.2, U7.64 (GPIO33)
SD1_CMD: C168.1, J5.3 (DI), P8.P$1, R28.1, R193.1
SD1_D0: C167.1, J5.7 (DO), P6.P$1, R27.1, R191.1
SD1_SCK: C169.1, J5.5 (SCLK), P7.P$1, R140.1, R192.1
SD2_CLK: R133.2, U7.19 (GPIO18)
SD2_CLK_C6: C165.1, IC1.25 (IO19), R82.2, R133.1
SD2_CMD: R34.2, U7.20 (GPIO19)
SD2_CMD_C6: C166.1, IC1.24 (IO18), R34.1, R81.2
SD2_D0: R135.2, U7.18 (GPIO17)
SD2_D0_C6: C164.1, IC1.26 (IO20), R83.2, R135.1
SD2_D1: R136.2, U7.17 (GPIO16)
SD2_D1_C6: C163.1, IC1.27 (IO21), R84.2, R136.1
SD2_D2: R137.2, U7.16 (GPIO15)
SD2_D2_C6: C69.1, IC1.28 (IO22), R85.2, R137.1
SD2_D3: R138.2, U7.15 (GPIO14)
SD2_D3_C6: C25.1, IC1.29 (IO23), R86.2, R138.1
SDCS: J5.2 (CS), P73.P$1, R29.1, R33.1
SHLR: J21.6, P40.P$1, R122.1, R123.2
SPI2_MISO: C172.2, J9.3, J9.3-3 (3), R332.2
SPI2_MOSI: C171.2, J9.4, J9.4-4 (4), R216.2
SPI2_SCK: C173.2, J9.2, J9.2-2 (2), R217.2
SPI_BOOT: C54.2, K3.2, R55.1, R91.2, U8.3 (C2)
STBYB: J21.26, P51.P$1, R63.1, R64.2
STC8_RXD: J8.2, R186.1
STC8_TXD: J8.1, R164.1
STC8_VDD_3V3: C158.2, C159.2, C160.2, IC8.5 (VOUT), J8.3, R189.1, U5.8 (VCC), U5.9 (VREF)
TXD0: R8.1, U7.69 (GPIO37)
TXD1: J2.2, U7.89 (GPIO47)
TXD3: Q1.2 (S), R52.2, U7.65 (GPIO34)
UART_IN_RXD3: J10.2, Q2.3 (D), R46.2
UART_IN_TXD3: J10.1, Q1.3 (D), R51.2
UPDN: J21.5, P41.P$1, R68.1, R108.2
USB1_D+: J1.A6, J1.B6, P2.P$1, R6.2
USB1_D-: J1.A7, J1.B7, P3.P$1, R7.2
USB2_D+: J16.A6, J16.B6, U7.50 (DP)
USB2_D-: J16.A7, J16.B7, U7.49 (DM)
VBAT: C4.2, J3.P$1, P9.P$1, Q3.5 (5_D), Q3.6 (6_D), Q3.7 (7_D), Q3.8 (8_D), Q3.9 (9_D), R17.1, R187.1, U2.3 (BAT)
VCC5V: C155.2, C156.2, D1.1, D1.2, D2.-, D007.-, D10.-, IC8.1 (VIN), P11.P$1, Q3.1 (1_S), Q3.2 (2_S), Q3.3 (3_S), Q5.1 (1_S), Q5.2 (2_S), Q5.3 (3_S), R78.2, R116.2
VCC5V_IN: C3.2, D4.-, D008.-, D11.-, Q3.4 (4_G), R17.2, R18.2, R47.2, R50.2, U2.4 (VCC)
VCCA: C43.1, C47.2, R23.1, U7.51 (VCCA)
VDD5V: C12.1, C74.2, C75.2, C79.2, C80.2, C90.1, C91.1, C149.2, C150.2, FB15.1, FB17.2, FB18.2, IC2.1 (VIN), IC3.1 (VIN), IC7.1 (VIN), J7.2, J7.4, J7.6, L2.1, L4.2, P5.P$1, Q5.5 (5_D), Q5.6 (6_D), Q5.7 (7_D), Q5.8 (8_D), Q5.9 (9_D), Q11.2 (S), R1.2, R24.2, R26.2, R61.2, R66.2, R165.1, R180.2, R181.2, R184.1, U9.4 (VIN), U16.5 (5_IN)
VDD5V_W: C88.1, J9.7, J9.7-7 (7), L4.1
VDDA: C7.1, C8.2, R19.1, U7.101 (VDDA)
VDDPST: C36.1, C55.1, R40.1, R110.1, U7.59 (VDDPST), U7.67 (VDDPST)
VDDPST_1: C73.1, C107.2, R36.1, U7.9 (VDDPST_1)
VDDPST_2: C41.1, C44.2, R37.1, U7.21 (VDDPST_2)
VDDPST_3: C45.1, C49.2, R38.1, U7.30 (VDDPST_3)
VDDPST_4: C50.1, C56.2, R39.1, U7.62 (VDDPST_4)
VDDPST_5: C60.1, C65.1, Q8.1 (G), Q9.1 (G), R69.1, R74.1, R75.1, R97.1, R98.1, R109.1, U7.85 (VDDPST_5)
VDDPST_6: C61.1, C71.2, R41.1, U7.96 (VDDPST_6)
VDDPST_DCDC: C5.1, C6.2, R12.1, U7.77 (VDDPST_DCDC)
VDDPST_LDO: C46.1, C48.2, R70.1, U7.75 (VDDPST_LDO)
VDD_1V2: C31.2, C32.2, C144.2, L6.2, R14.1, R42.2, R43.2, R44.2
VDD_3V3: C1.2, C10.2, C16.2, C20.2, C26.2, C27.2, C136.2, FB16.1, FPC2.5, IC4.1 (VIN), J2.3, J5.4 (VDD), J7.1, J7.3, J7.5, J13.3, L1.2, L3.2, P13.P$1, Q1.1 (G), Q2.1 (G), Q10.2 (S), R2.1, R12.2, R15.2, R19.2, R20.2, R22.1, R23.2, R27.2, R28.2, R29.2, R30.2, R36.2, R37.2, R38.2, R39.2, R41.2, R45.1, R52.1, R53.2, R54.1, R58.1, R59.1, R65.2, R70.2, R71.2, R76.2, R91.1, R93.1, R94.1, R106.1, R107.2, R110.2, R140.2, U1.7 (VCC)
VDD_3V3_A: C70.1, C170.1, J9.5, J9.5-5 (5), L3.1
VDD_FLASH: C39.1, C40.1, C51.1, IC11.8 (VCC), R105.1, R107.1, R333.2
VDD_HP_0: C108.1, C112.2, R42.1, U7.26 (VDD_HP_0)
VDD_HP_2: C113.1, C114.2, R43.1, U7.76 (VDD_HP_2)
VDD_HP_3: C115.1, C116.2, R44.1, U7.91 (VDD_HP_3)
VDD_MIPI_DPHY: C62.1, C63.1, C64.1, R80.1, U7.41 (VDD_MIPI_DPHY)
VOLN: C106.2, FB11.2, FB12.2, J4.P$2, P55.P$1
VOLP: C105.2, FB9.2, FB10.2, J4.P$1, P54.P$1
VORN: C68.2, FB3.2, FB7.2, J6.P$2, P32.P$1
VORP: C67.2, FB2.2, FB8.2, J6.P$1, P26.P$1
XTAL_N: C34.2, U7.99 (XTAL_N), Y2.3 (CRYSTAL_2)
XTAL_P: C33.1, U7.100 (XTAL_P), Y2.1 (CRYSTAL_1)
XVCLK: C87.2, FPC1.11, Y3.3 (3_OUT)

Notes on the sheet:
BOOT
RESET
HIG: SPI Boot
LOW: Download Boot
HIG: ESP32-P4 Enable
LOW: ESP32-P4 Off
Power_LED
USB interface
USB TO UART
Battery and control
ESP32-C6
7.0 inch IPS interface
SD card
Wireless module
UART & I2C & GPIO extensions
PDM MIC
UART_5V_IN
I2C_OUT
UART0_OUT
ESP32-P4
ESP32-P4_POWER
CSI_Interface
I led=200mV/0.75=160mA
DSI_LED Driver
Audio_OUT
DC-DC:5V to 3V3
DC-DC:5V to 1V2
Power SW
LCD_POWER
Charge indicator control
Audio_ADC/DAC
LDO:5V to 3V3(AUDIO POWER)
ESP32 P4-Advance HMI Display 10.1 V1.0

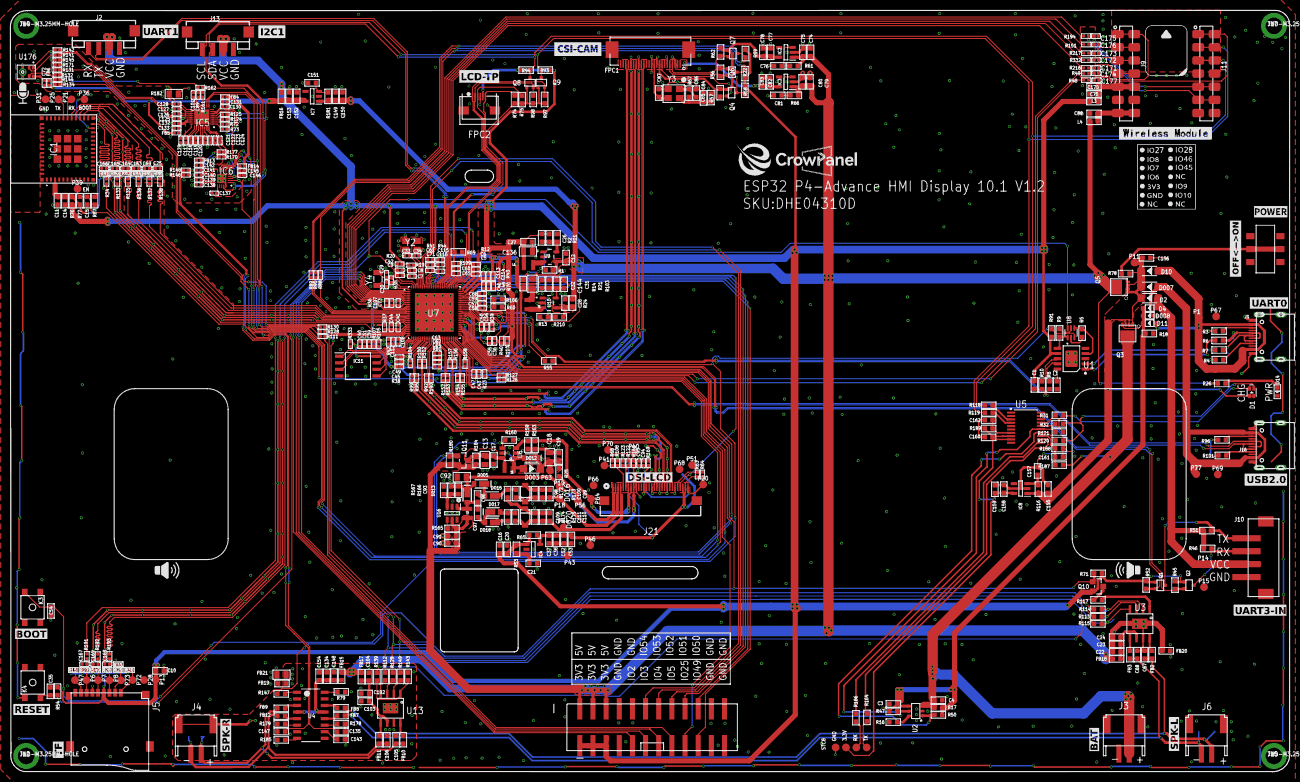
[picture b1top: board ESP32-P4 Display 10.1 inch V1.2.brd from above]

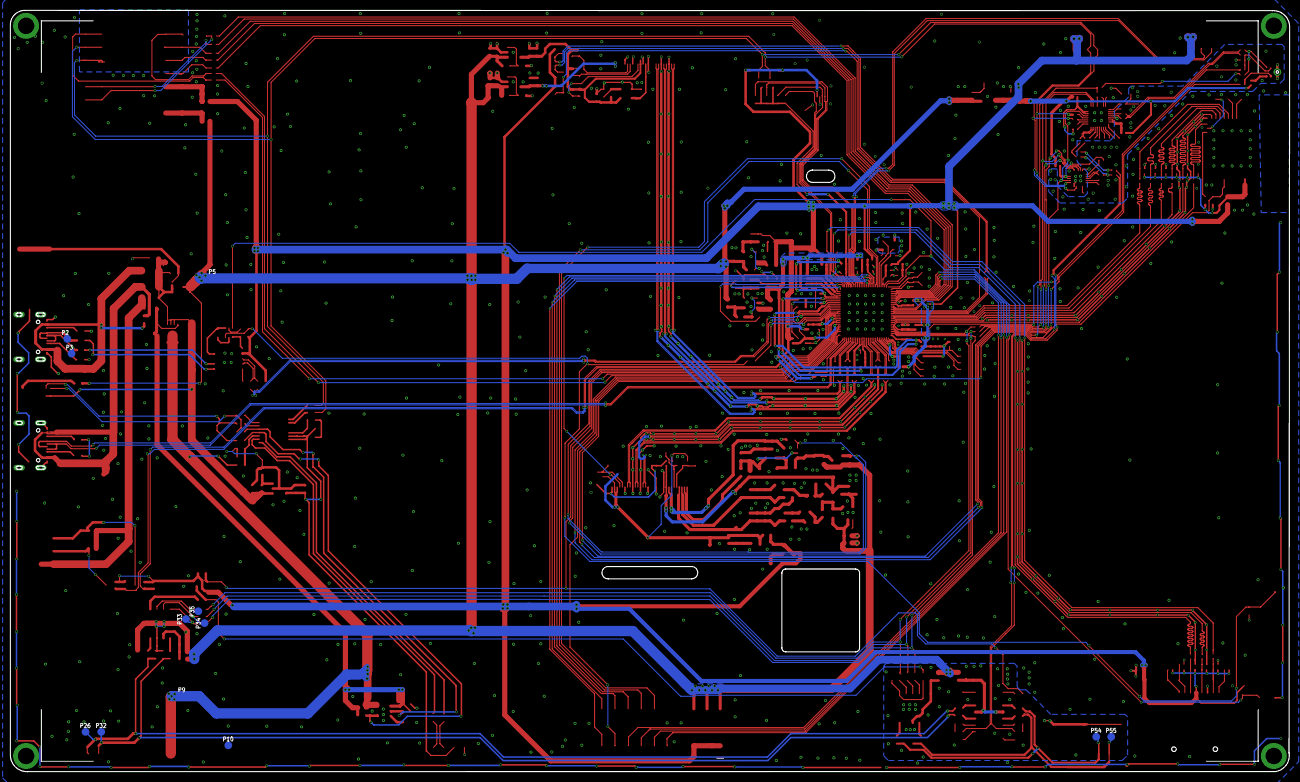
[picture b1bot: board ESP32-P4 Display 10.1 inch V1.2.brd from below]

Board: 2 copper layers, 247.0 x 147.0 mm, 522 parts (12 on the bottom side), 315 nets.

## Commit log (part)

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2025-11-20 Update readme with compilation info and download link
    Added program download link and clarified compilation.
2026-03-18 add arduino
2026-05-12 sync idf lesson13
2026-06-04 sync example/V1.1 1.2
2026-06-04 sync example/V1.2

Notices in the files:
parts and their libraries:
SparkFun-Coils: Licensing: Creative Commons ShareAlike 4.0 International - https://creativecommons.org/licenses/by-sa/4.0
